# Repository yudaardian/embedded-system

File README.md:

# embedded-system
project embedded system

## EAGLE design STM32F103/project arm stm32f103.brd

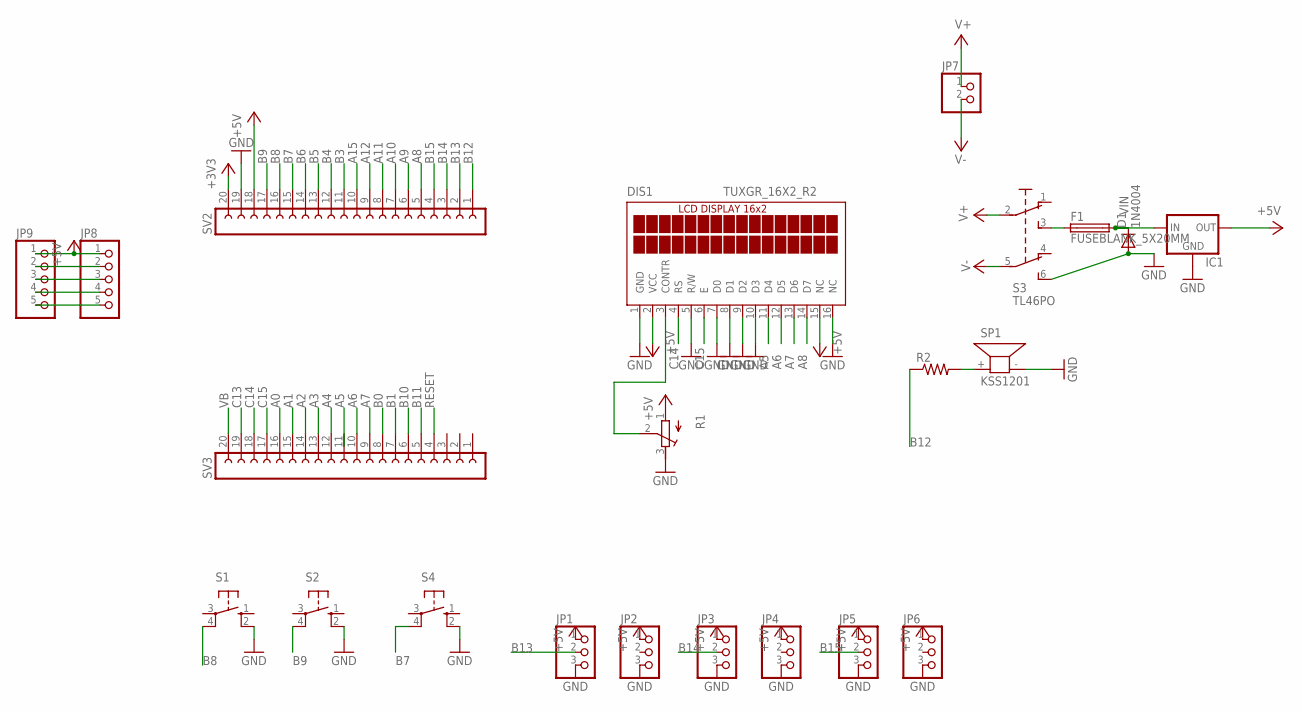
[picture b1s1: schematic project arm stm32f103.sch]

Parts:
D1: 1N4004; DO41-10
DIS1: TUXGR_16X2_R2
F1: FUSEBLANK_5X20MM; FUSE_HOLDER_5X20MM
IC1: 78XXL
JP1, JP2, JP3, JP4, JP5, JP6: PINHD-1X3; 1X03
JP7: PINHD-1X2; 1X02
JP8, JP9: PINHD-1X5/90; 1X05/90
R1: R-TRIMM3339P; RTRIM3339P
R2: R-US_0204/7; 0204/7
S1, S2, S4: 10-XX; B3F-10XX
S3: TL46PO; TL4XPO
SP1: KSS1201
SV2, SV3: FE20-1; FE20

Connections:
+3V3: SV2.20
+5V: DIS1.2 (VCC), DIS1.15 (NC), IC1.OUT, JP1.1, JP2.1, JP3.1, JP4.1, JP5.1, JP6.1, JP8.1, JP9.1, R1.1 (E), SV2.18
A0: SV3.16
A1: SV3.15
A2: SV3.14
A3: SV3.13
A4: SV3.12
A5: DIS1.11 (D4)
A6: DIS1.12 (D5), SV3.10
A7: DIS1.13 (D6), SV3.9
A8: DIS1.14 (D7), SV2.5
A9: SV2.6
A10: SV2.7
A11: SV2.8
A12: SV2.9
A15: SV2.10
B0: SV3.8
B1: SV3.7
B3: SV2.11
B4: SV2.12
B5: SV2.13
B6: SV2.14
B7: S4.4 (P1), SV2.15
B8: S1.4 (P1), SV2.16
B9: S2.4 (P1), SV2.17
B10: SV3.6
B11: SV3.5
B12: R2.1, SV2.1
B13: JP1.2, SV2.2
B14: JP3.2, SV2.3
B15: JP5.2, SV2.4
C13: SV3.19
C14: DIS1.4 (RS), SV3.18
C15: DIS1.6 (E), SV3.17
GND: D1.A, DIS1.1 (GND), DIS1.5 (R/W), DIS1.7 (D0), DIS1.8 (D1), DIS1.9 (D2), DIS1.10 (D3), DIS1.16 (NC), IC1.GND, JP1.3, JP2.3, JP3.3, JP4.3, JP5.3, JP6.3, R1.3 (A), S1.2 (S1), S2.2 (S1), S3.6 (S1), S4.2 (S1), SP1.- (2), SV2.19
unnamed: R2.2, SP1.+ (1)
unnamed: F1.1, S3.3 (S)
unnamed: DIS1.3 (CONTR), R1.2 (S)
unnamed: JP8.2, JP9.2
unnamed: JP8.3, JP9.3
unnamed: JP8.4, JP9.4
unnamed: JP8.5, JP9.5
RESET: SV3.4
V+: JP7.1, S3.2
V-: JP7.2, S3.5 (P1)
VB: SV3.20
VIN: D1.C, F1.2, IC1.IN

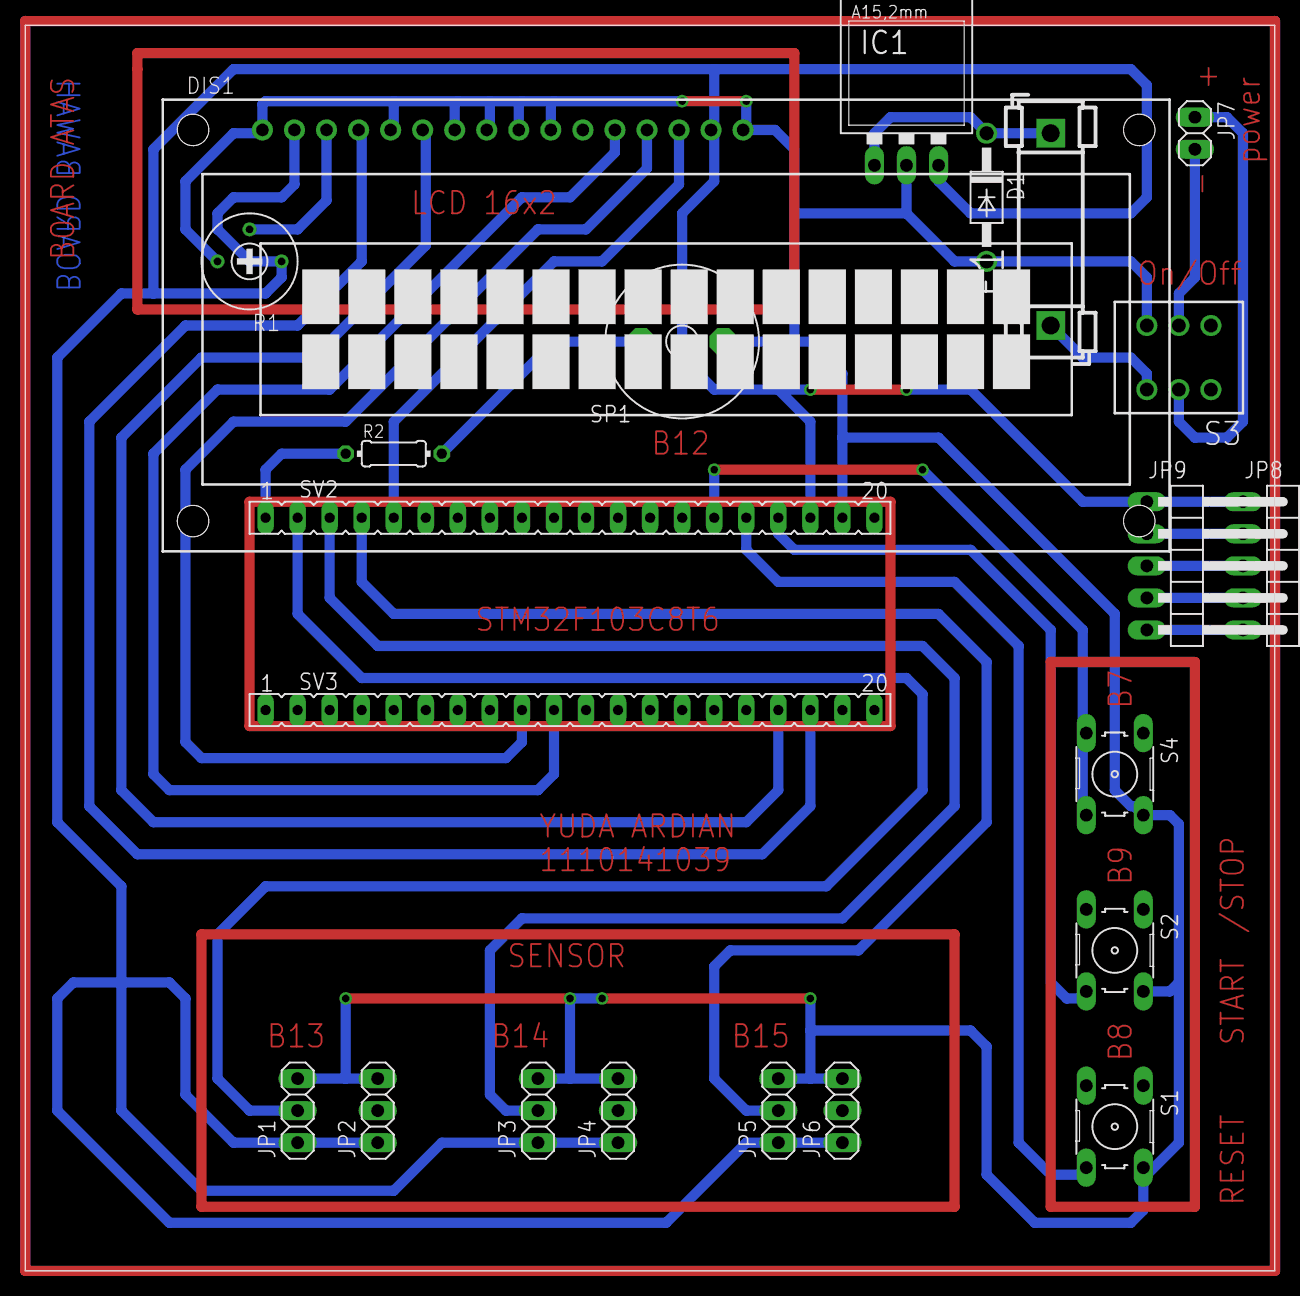
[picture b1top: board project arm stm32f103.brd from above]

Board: 2 copper layers, 99.0 x 98.7 mm, 22 parts (0 on the bottom side), 24 nets.

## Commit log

2017-11-28 Create code project
